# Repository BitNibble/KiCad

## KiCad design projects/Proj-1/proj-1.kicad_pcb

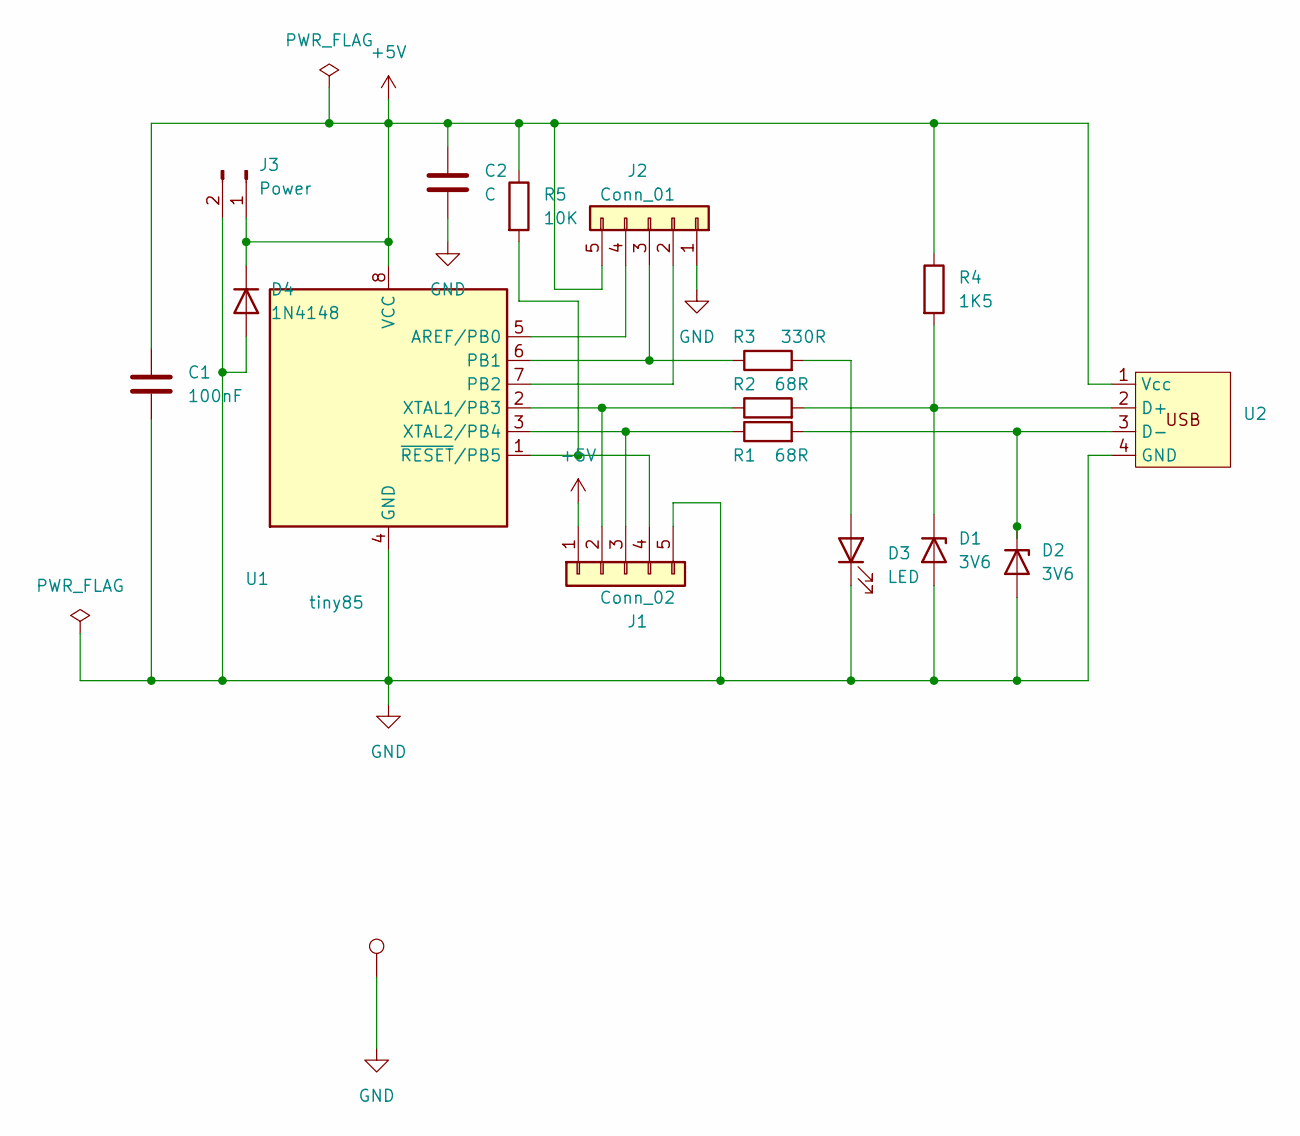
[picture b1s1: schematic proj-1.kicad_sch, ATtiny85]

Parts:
C1: 100nF; C_Disc_D5.0mm_W2.5mm_P5.00mm
C2: C; C_Disc_D3.0mm_W1.6mm_P2.50mm
D1, D2: 3V6; D_SOD-123
D3: LED; LED_D3.0mm
D4: 1N4148; D_1210_3225Metric
J1: Conn_02; JST_EH_B5B-EH-A_1x05_P2.50mm_Vertical
J2: Conn_01; JST_EH_B5B-EH-A_1x05_P2.50mm_Vertical
J3: Power; PinHeader_1x02_P2.54mm_Vertical
R1, R2: 68R; R_0805_2012Metric_Pad1.20x1.40mm_HandSolder
R3: 330R; R_0805_2012Metric_Pad1.20x1.40mm_HandSolder
R4: 1K5; R_0805_2012Metric_Pad1.20x1.40mm_HandSolder
R5: 10K; R_0805_2012Metric_Pad1.20x1.40mm_HandSolder
TP1: TestPoint; TestPoint_Loop_D2.50mm_Drill1.0mm_LowProfile
U1: tiny85; DIP-8_W7.62mm
U2: PCB_USB

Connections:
+5V: C1.1, C2.1, D4.1 (K), J1.1, J2.5, J3.1, R4.1, R5.1, U1.8 (VCC), U2.1 (Vcc)
GND: C1.2, C2.2, D1.2 (A), D2.2 (A), D3.1 (K), D4.2 (A), J1.5, J2.1, J3.2, TP1.1, U1.4 (GND), U2.4 (GND)
unnamed: D1.1 (K), R2.2, R4.2, U2.2 (D+)
unnamed: D2.1 (K), R1.2, U2.3 (D-)
unnamed: D3.2 (A), R3.2
unnamed: J1.2, R2.1, U1.2 (XTAL1/PB3)
unnamed: J1.3, R1.1, U1.3 (XTAL2/PB4)
unnamed: J1.4, R5.2, U1.1 (~RESET/PB5)
unnamed: J2.2, U1.7 (PB2)
unnamed: J2.3, R3.1, U1.6 (PB1)
unnamed: J2.4, U1.5 (AREF/PB0)

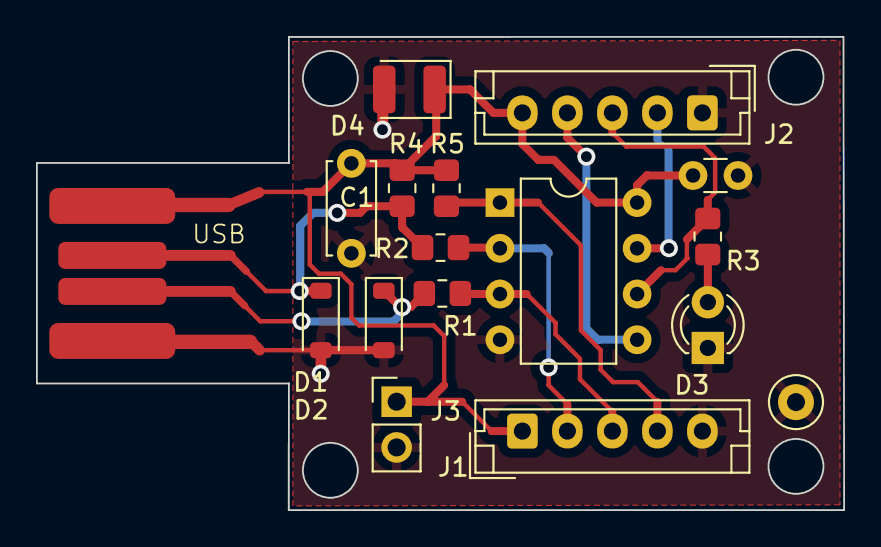
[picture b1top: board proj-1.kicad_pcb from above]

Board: 2 copper layers, 44.8 x 26.3 mm, 17 parts (0 on the bottom side), 11 nets.

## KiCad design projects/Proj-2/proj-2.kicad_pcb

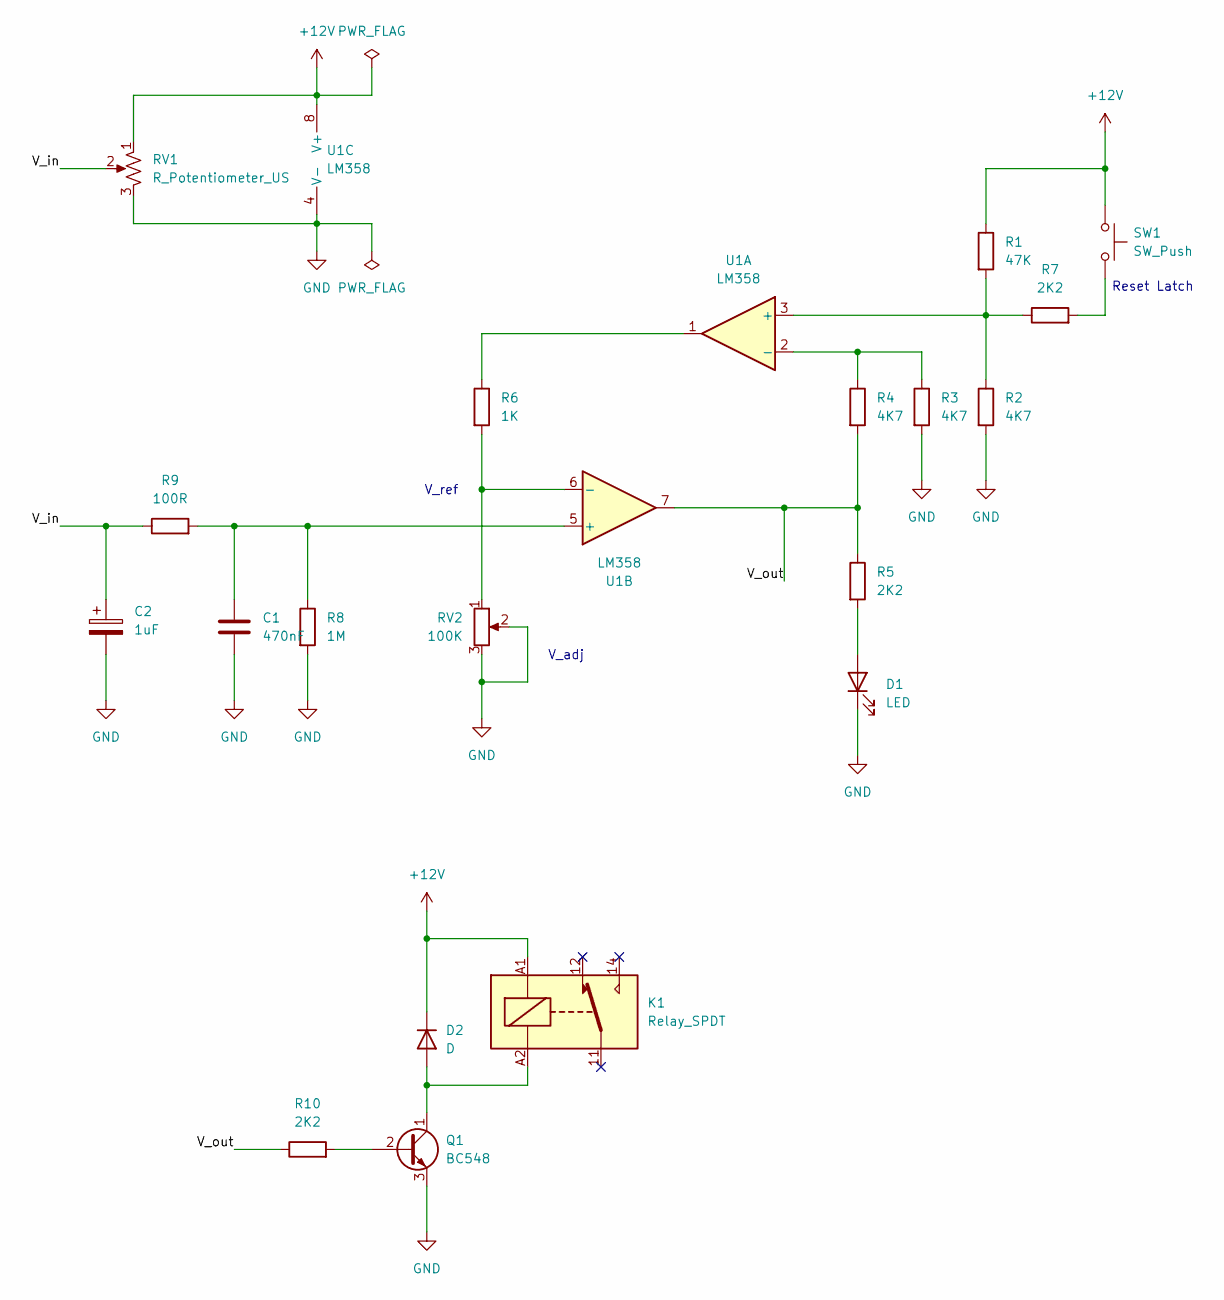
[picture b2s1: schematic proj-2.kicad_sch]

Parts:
C1: 470nF
C2: 1uF
D1: LED; LED_D5.0mm
D2: D; D_DO-35_SOD27_P7.62mm_Horizontal
K1: Relay_SPDT; Relay_1-Form-C_Schrack-RYII_RM3.2mm
Q1: BC548; TO-92_Inline
R1: 47K; R_Axial_DIN0207_L6.3mm_D2.5mm_P10.16mm_Horizontal
R2, R3, R4: 4K7; R_Axial_DIN0207_L6.3mm_D2.5mm_P10.16mm_Horizontal
R5, R7, R10: 2K2; R_Axial_DIN0207_L6.3mm_D2.5mm_P10.16mm_Horizontal
R6: 1K; R_Axial_DIN0207_L6.3mm_D2.5mm_P10.16mm_Horizontal
R8: 1M; R_Axial_DIN0207_L6.3mm_D2.5mm_P10.16mm_Horizontal
R9: 100R; R_Axial_DIN0207_L6.3mm_D2.5mm_P10.16mm_Horizontal
RV1: R_Potentiometer_US; Potentiometer_Alps_RK163_Single_Horizontal
RV2: 100K; Potentiometer_Bourns_3266Y_Vertical
SW1: SW_Push; SW_PUSH_6mm_H13mm
U1: LM358; CERDIP-8_W7.62mm_SideBrazed_LongPads

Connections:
+12V: D2.1 (K), K1.A1, R1.1, RV1.1, SW1.1, U1.8 (V+)
/V_in: C2.1, R9.1, RV1.2
/V_out: R4.2, R5.1, R10.1, U1.7
GND: C1.2, C2.2, D1.1 (K), Q1.3 (E), R2.2, R3.2, R8.2, RV1.3, RV2.2, RV2.3, U1.4 (V-)
unnamed: D1.2 (A), R5.2
unnamed: D2.2 (A), K1.A2, Q1.1 (C)
unnamed: Q1.2 (B), R10.2
unnamed: R6.1, U1.1
unnamed: R7.2, SW1.2
unnamed: R1.2, R2.1, R7.1, U1.3 (+)
unnamed: R3.1, R4.1, U1.2 (-)
unnamed: C1.1, R8.1, R9.2, U1.5 (+)
unnamed: R6.2, RV2.1, U1.6 (-)

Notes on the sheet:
V_ref
V_adj
Reset Latch

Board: 2 copper layers, 18 parts (0 on the bottom side), 13 nets, no tracks yet.

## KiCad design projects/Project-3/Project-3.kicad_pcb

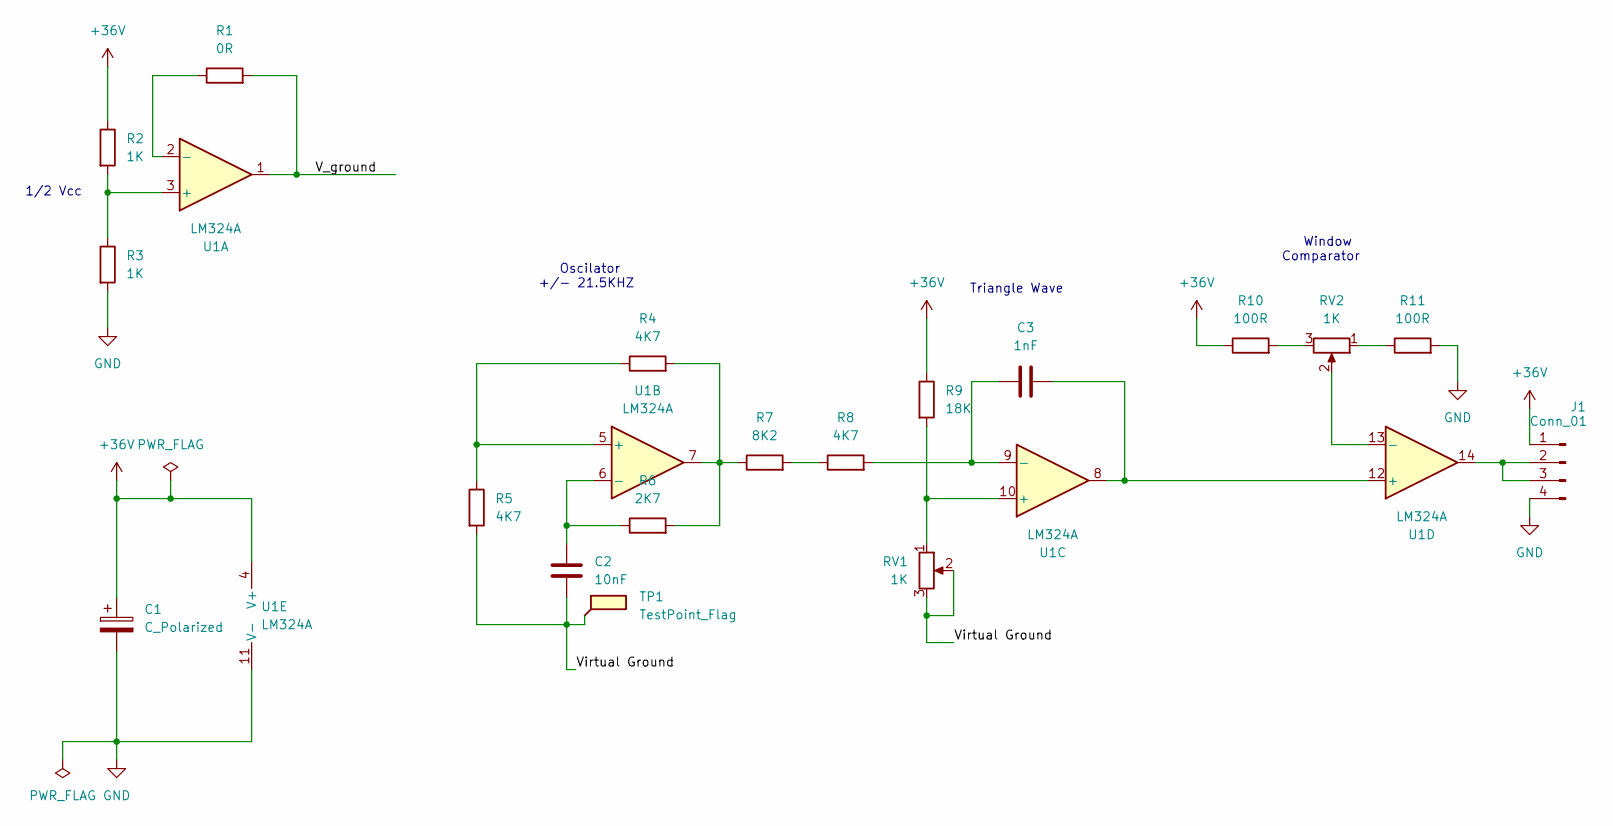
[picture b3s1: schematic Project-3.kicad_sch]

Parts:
C1: C_Polarized; CP_Radial_D18.0mm_P7.50mm
C2: 10nF; C_Disc_D5.0mm_W2.5mm_P2.50mm
C3: 1nF; C_Disc_D5.0mm_W2.5mm_P2.50mm
J1: Conn_01; Wago_734-134_1x04_P3.50mm_Vertical
R1: 0R; R_Axial_DIN0207_L6.3mm_D2.5mm_P7.62mm_Horizontal
R2, R3: 1K; R_Axial_DIN0207_L6.3mm_D2.5mm_P7.62mm_Horizontal
R4, R5, R8: 4K7; R_Axial_DIN0207_L6.3mm_D2.5mm_P7.62mm_Horizontal
R6: 2K7; R_Axial_DIN0207_L6.3mm_D2.5mm_P7.62mm_Horizontal
R7: 8K2; R_Axial_DIN0207_L6.3mm_D2.5mm_P7.62mm_Horizontal
R9: 18K; R_Axial_DIN0207_L6.3mm_D2.5mm_P7.62mm_Horizontal
R10, R11: 100R; R_Axial_DIN0207_L6.3mm_D2.5mm_P10.16mm_Horizontal
RV1: 1K; Potentiometer_Bourns_3266Y_Vertical
RV2: 1K; Potentiometer_TT_P0915N
TP1: TestPoint_Flag; TestPoint_Loop_D2.50mm_Drill1.0mm
U1: LM324A; CERDIP-14_W7.62mm_SideBrazed_Socket

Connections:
+36V: C1.1, J1.1, R2.1, R9.1, R10.1, U1.4 (V+)
/V_ground: R1.2, U1.1
/Virtual Ground: C2.2, R5.2, RV1.2, RV1.3, TP1.1
GND: C1.2, J1.4, R3.2, R11.2, U1.11 (V-)
unnamed: J1.2, J1.3, U1.14
unnamed: R4.2, R6.2, R7.1, U1.7
unnamed: R7.2, R8.1
unnamed: R10.2, RV2.3
unnamed: R11.1, RV2.1
unnamed: R2.2, R3.1, U1.3 (+)
unnamed: R1.1, U1.2 (-)
unnamed: R4.1, R5.1, U1.5 (+)
unnamed: C2.1, R6.1, U1.6 (-)
unnamed: R9.2, RV1.1, U1.10 (+)
unnamed: C3.1, R8.2, U1.9 (-)
unnamed: C3.2, U1.8, U1.12 (+)
unnamed: RV2.2, U1.13 (-)

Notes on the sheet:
1/2 Vcc
Oscilator +/- 21.5KHZ
Triangle Wave
Window Comparator

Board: 2 copper layers, 19 parts (0 on the bottom side), 17 nets, no tracks yet.

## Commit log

2024-03-14 play with kicad-1
